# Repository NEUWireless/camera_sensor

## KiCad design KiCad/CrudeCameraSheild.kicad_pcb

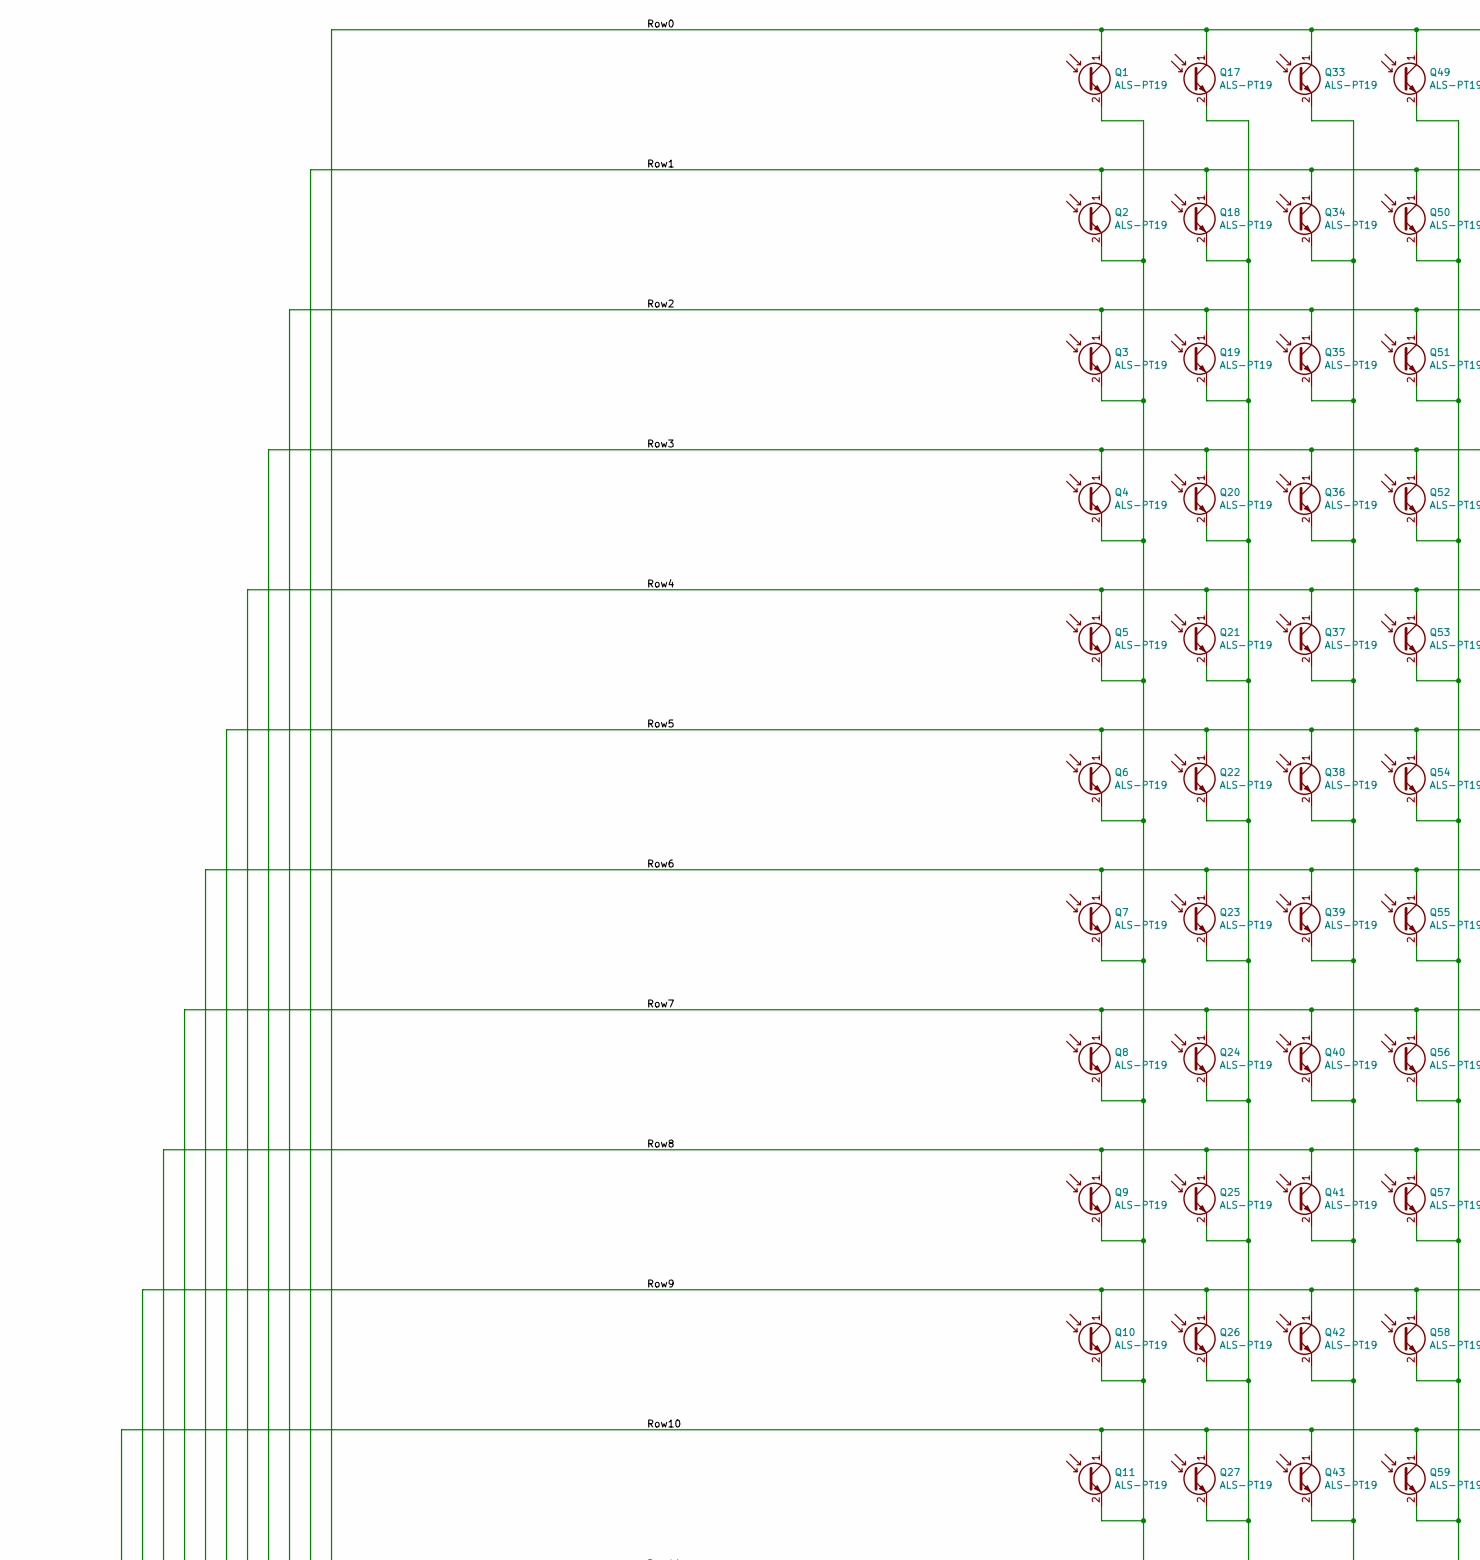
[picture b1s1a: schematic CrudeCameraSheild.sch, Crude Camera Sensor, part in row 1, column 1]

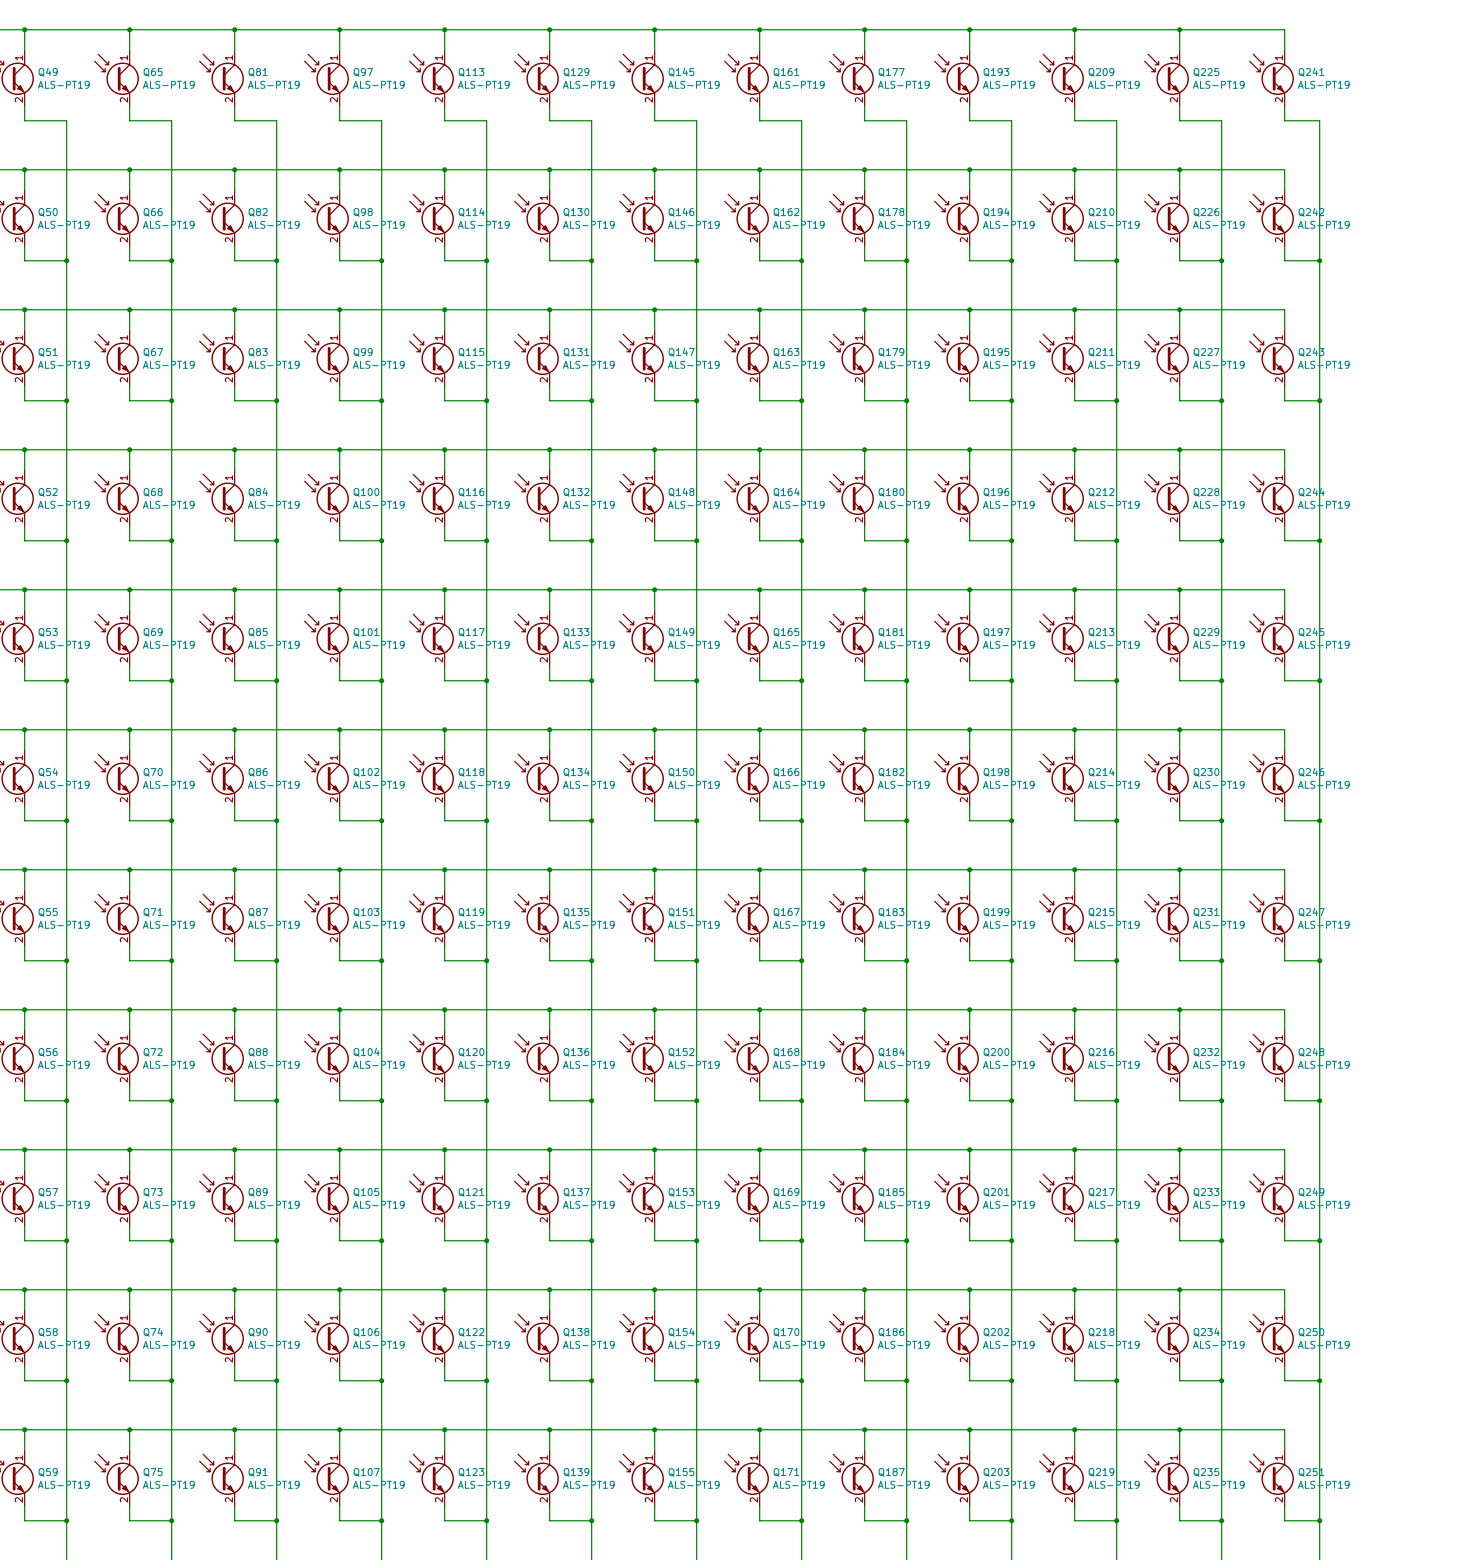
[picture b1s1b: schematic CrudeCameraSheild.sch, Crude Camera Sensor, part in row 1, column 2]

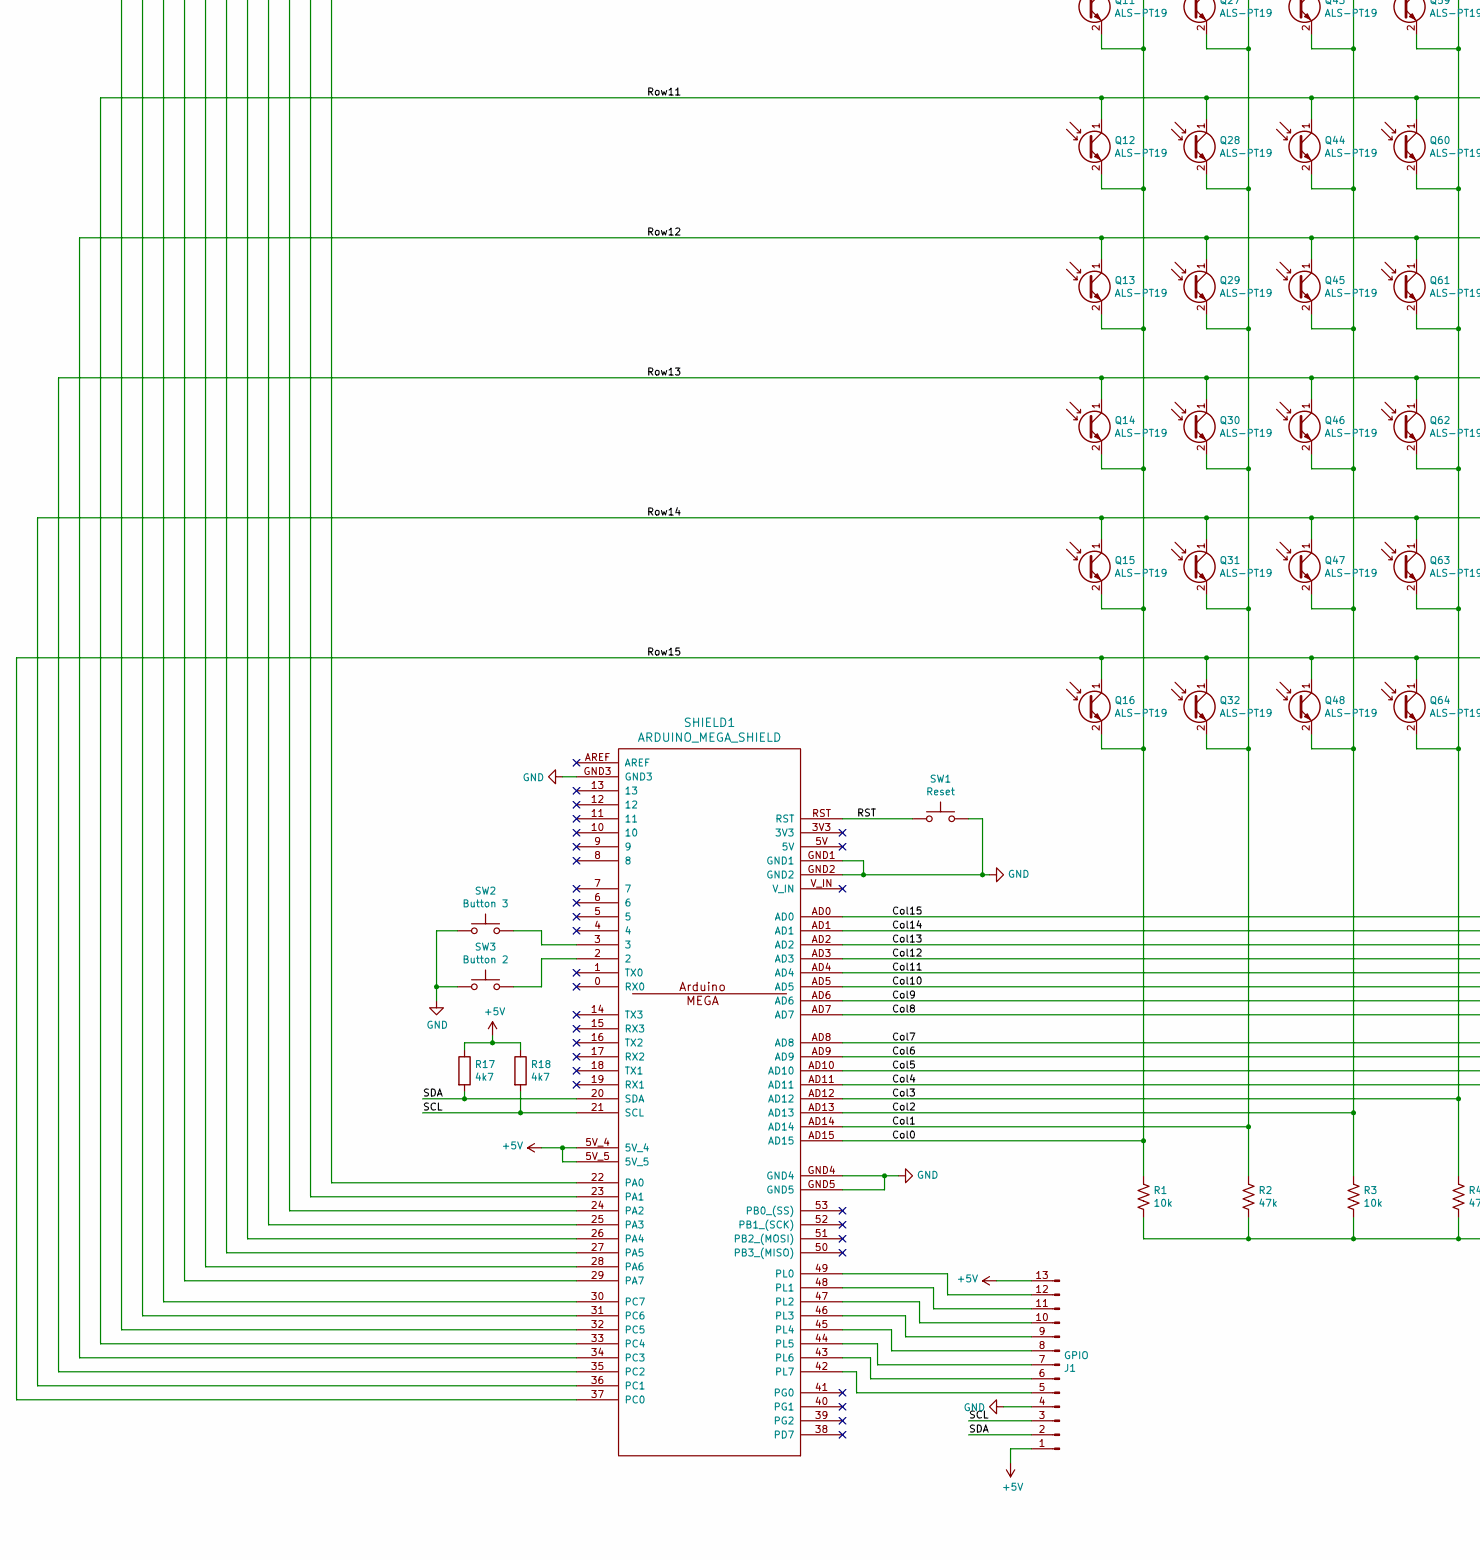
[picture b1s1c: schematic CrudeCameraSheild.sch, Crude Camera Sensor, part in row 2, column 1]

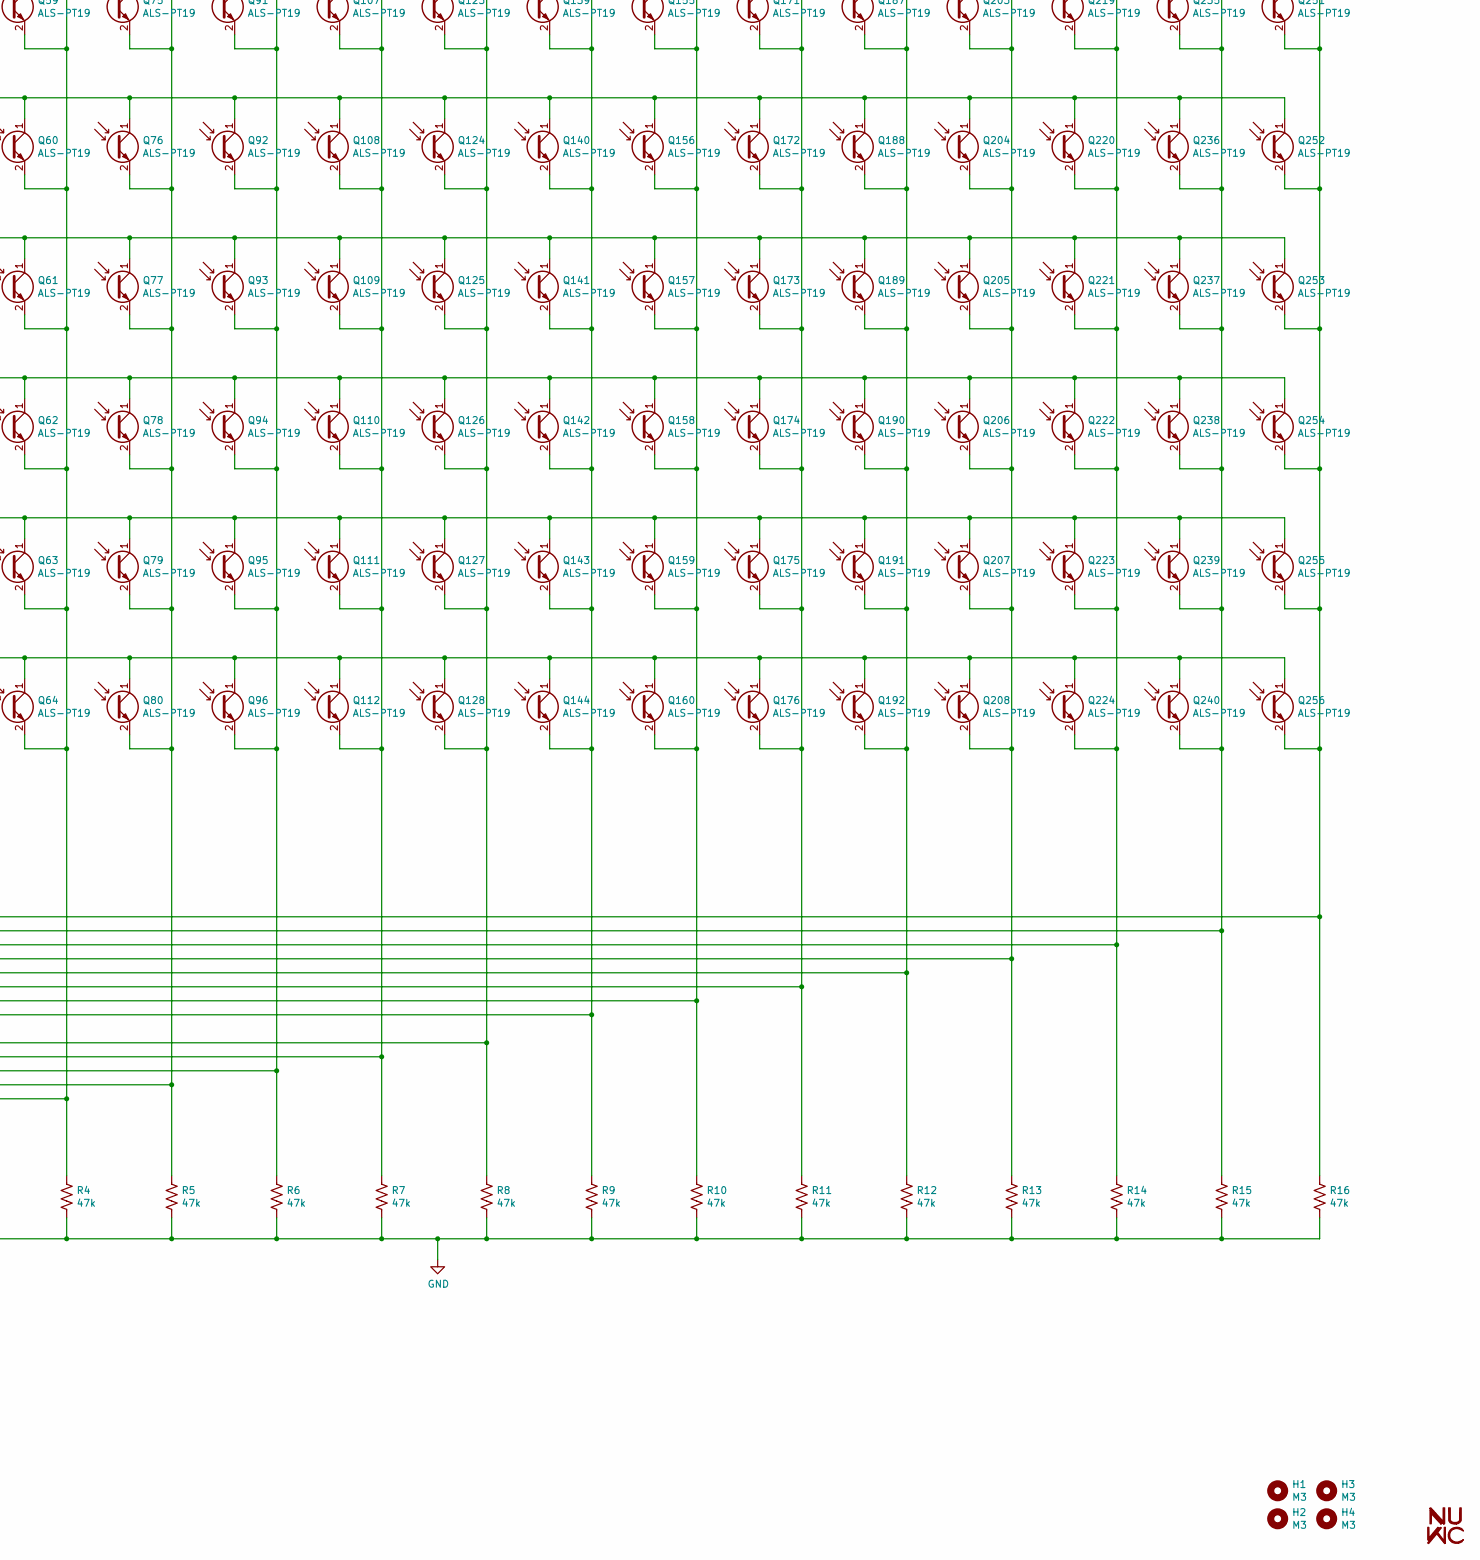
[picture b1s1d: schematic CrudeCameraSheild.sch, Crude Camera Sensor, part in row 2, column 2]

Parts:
G1: LOGO; WirelessClub
H1, H2, H3, H4: M3; MountingHole_3.2mm_M3
J1: GPIO; PinHeader_1x13_P2.54mm_Horizontal
Q1, Q2, Q3, Q4, Q5, Q6, Q7, Q8, Q9, Q10, Q11, Q12, Q13, Q14, Q15, Q16, Q17, Q18, Q19, Q20, Q21, Q22, Q23, Q24, Q25, Q26, Q27, Q28, Q29, Q30, Q31, Q32, Q33, Q34, Q35, Q36, Q37, Q38, Q39, Q40, Q41, Q42, Q43, Q44, Q45, Q46, Q47, Q48, Q49, Q50, Q51, Q52, Q53, Q54, Q55, Q56, Q57, Q58, Q59, Q60, Q61, Q62, Q63, Q64, Q65, Q66, Q67, Q68, Q69, Q70, Q71, Q72, Q73, Q74, Q75, Q76, Q77, Q78, Q79, Q80, Q81, Q82, Q83, Q84, Q85, Q86, Q87, Q88, Q89, Q90, Q91, Q92, Q93, Q94, Q95, Q96, Q97, Q98, Q99, Q100, Q101, Q102, Q103, Q104, Q105, Q106, Q107, Q108, Q109, Q110, Q111, Q112, Q113, Q114, Q115, Q116, Q117, Q118, Q119, Q120, Q121, Q122, Q123, Q124, Q125, Q126, Q127, Q128, Q129, Q130, Q131, Q132, Q133, Q134, Q135, Q136, Q137, Q138, Q139, Q140, Q141, Q142, Q143, Q144, Q145, Q146, Q147, Q148, Q149, Q150, Q151, Q152, Q153, Q154, Q155, Q156, Q157, Q158, Q159, Q160, Q161, Q162, Q163, Q164, Q165, Q166, Q167, Q168, Q169, Q170, Q171, Q172, Q173, Q174, Q175, Q176, Q177, Q178, Q179, Q180, Q181, Q182, Q183, Q184, Q185, Q186, Q187, Q188, Q189, Q190, Q191, Q192, Q193, Q194, Q195, Q196, Q197, Q198, Q199, Q200, Q201, Q202, Q203, Q204, Q205, Q206, Q207, Q208, Q209, Q210, Q211, Q212, Q213, Q214, Q215, Q216, Q217, Q218, Q219, Q220, Q221, Q222, Q223, Q224, Q225, Q226, Q227, Q228, Q229, Q230, Q231, Q232, Q233, Q234, Q235, Q236, Q237, Q238, Q239, Q240, Q241, Q242, Q243, Q244, Q245, Q246, Q247, Q248, Q249, Q250, Q251, Q252, Q253, Q254, Q255, Q256: ALS-PT19; LED_0603_1608Metric_Pad1.05x0.95mm_HandSolder
R1, R3: 10k; R_1206_3216Metric_Pad1.42x1.75mm_HandSolder
R2, R4, R5, R6, R7, R8, R9, R10, R11, R12, R13, R14, R15, R16: 47k; R_1206_3216Metric_Pad1.42x1.75mm_HandSolder
R17, R18: 4k7; R_1206_3216Metric_Pad1.42x1.75mm_HandSolder
SHIELD1: ARDUINO_MEGA_SHIELD; ARDUINO MEGA SHIELD
SW1: Reset; SW_Push_1P1T_NO_6x6mm_H9.5mm
SW2: Button 3; SW_Push_1P1T_NO_6x6mm_H9.5mm
SW3: Button 2; SW_Push_1P1T_NO_6x6mm_H9.5mm

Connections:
+5V: J1.1, J1.13, R17.1, R18.1, SHIELD1.5V_4, SHIELD1.5V_5
/Col0: Q1.2 (E), Q2.2 (E), Q3.2 (E), Q4.2 (E), Q5.2 (E), Q6.2 (E), Q7.2 (E), Q8.2 (E), Q9.2 (E), Q10.2 (E), Q11.2 (E), Q12.2 (E), Q13.2 (E), Q14.2 (E), Q15.2 (E), Q16.2 (E), R1.1, SHIELD1.AD15
/Col1: Q17.2 (E), Q18.2 (E), Q19.2 (E), Q20.2 (E), Q21.2 (E), Q22.2 (E), Q23.2 (E), Q24.2 (E), Q25.2 (E), Q26.2 (E), Q27.2 (E), Q28.2 (E), Q29.2 (E), Q30.2 (E), Q31.2 (E), Q32.2 (E), R2.1, SHIELD1.AD14
/Col2: Q33.2 (E), Q34.2 (E), Q35.2 (E), Q36.2 (E), Q37.2 (E), Q38.2 (E), Q39.2 (E), Q40.2 (E), Q41.2 (E), Q42.2 (E), Q43.2 (E), Q44.2 (E), Q45.2 (E), Q46.2 (E), Q47.2 (E), Q48.2 (E), R3.1, SHIELD1.AD13
/Col3: Q49.2 (E), Q50.2 (E), Q51.2 (E), Q52.2 (E), Q53.2 (E), Q54.2 (E), Q55.2 (E), Q56.2 (E), Q57.2 (E), Q58.2 (E), Q59.2 (E), Q60.2 (E), Q61.2 (E), Q62.2 (E), Q63.2 (E), Q64.2 (E), R4.1, SHIELD1.AD12
/Col4: Q65.2 (E), Q66.2 (E), Q67.2 (E), Q68.2 (E), Q69.2 (E), Q70.2 (E), Q71.2 (E), Q72.2 (E), Q73.2 (E), Q74.2 (E), Q75.2 (E), Q76.2 (E), Q77.2 (E), Q78.2 (E), Q79.2 (E), Q80.2 (E), R5.1, SHIELD1.AD11
/Col5: Q81.2 (E), Q82.2 (E), Q83.2 (E), Q84.2 (E), Q85.2 (E), Q86.2 (E), Q87.2 (E), Q88.2 (E), Q89.2 (E), Q90.2 (E), Q91.2 (E), Q92.2 (E), Q93.2 (E), Q94.2 (E), Q95.2 (E), Q96.2 (E), R6.1, SHIELD1.AD10
/Col6: Q97.2 (E), Q98.2 (E), Q99.2 (E), Q100.2 (E), Q101.2 (E), Q102.2 (E), Q103.2 (E), Q104.2 (E), Q105.2 (E), Q106.2 (E), Q107.2 (E), Q108.2 (E), Q109.2 (E), Q110.2 (E), Q111.2 (E), Q112.2 (E), R7.1, SHIELD1.AD9
/Col7: Q113.2 (E), Q114.2 (E), Q115.2 (E), Q116.2 (E), Q117.2 (E), Q118.2 (E), Q119.2 (E), Q120.2 (E), Q121.2 (E), Q122.2 (E), Q123.2 (E), Q124.2 (E), Q125.2 (E), Q126.2 (E), Q127.2 (E), Q128.2 (E), R8.1, SHIELD1.AD8
/Col8: Q129.2 (E), Q130.2 (E), Q131.2 (E), Q132.2 (E), Q133.2 (E), Q134.2 (E), Q135.2 (E), Q136.2 (E), Q137.2 (E), Q138.2 (E), Q139.2 (E), Q140.2 (E), Q141.2 (E), Q142.2 (E), Q143.2 (E), Q144.2 (E), R9.1, SHIELD1.AD7
/Col9: Q145.2 (E), Q146.2 (E), Q147.2 (E), Q148.2 (E), Q149.2 (E), Q150.2 (E), Q151.2 (E), Q152.2 (E), Q153.2 (E), Q154.2 (E), Q155.2 (E), Q156.2 (E), Q157.2 (E), Q158.2 (E), Q159.2 (E), Q160.2 (E), R10.1, SHIELD1.AD6
/Col10: Q161.2 (E), Q162.2 (E), Q163.2 (E), Q164.2 (E), Q165.2 (E), Q166.2 (E), Q167.2 (E), Q168.2 (E), Q169.2 (E), Q170.2 (E), Q171.2 (E), Q172.2 (E), Q173.2 (E), Q174.2 (E), Q175.2 (E), Q176.2 (E), R11.1, SHIELD1.AD5
/Col11: Q177.2 (E), Q178.2 (E), Q179.2 (E), Q180.2 (E), Q181.2 (E), Q182.2 (E), Q183.2 (E), Q184.2 (E), Q185.2 (E), Q186.2 (E), Q187.2 (E), Q188.2 (E), Q189.2 (E), Q190.2 (E), Q191.2 (E), Q192.2 (E), R12.1, SHIELD1.AD4
/Col12: Q193.2 (E), Q194.2 (E), Q195.2 (E), Q196.2 (E), Q197.2 (E), Q198.2 (E), Q199.2 (E), Q200.2 (E), Q201.2 (E), Q202.2 (E), Q203.2 (E), Q204.2 (E), Q205.2 (E), Q206.2 (E), Q207.2 (E), Q208.2 (E), R13.1, SHIELD1.AD3
/Col13: Q209.2 (E), Q210.2 (E), Q211.2 (E), Q212.2 (E), Q213.2 (E), Q214.2 (E), Q215.2 (E), Q216.2 (E), Q217.2 (E), Q218.2 (E), Q219.2 (E), Q220.2 (E), Q221.2 (E), Q222.2 (E), Q223.2 (E), Q224.2 (E), R14.1, SHIELD1.AD2
/Col14: Q225.2 (E), Q226.2 (E), Q227.2 (E), Q228.2 (E), Q229.2 (E), Q230.2 (E), Q231.2 (E), Q232.2 (E), Q233.2 (E), Q234.2 (E), Q235.2 (E), Q236.2 (E), Q237.2 (E), Q238.2 (E), Q239.2 (E), Q240.2 (E), R15.1, SHIELD1.AD1
/Col15: Q241.2 (E), Q242.2 (E), Q243.2 (E), Q244.2 (E), Q245.2 (E), Q246.2 (E), Q247.2 (E), Q248.2 (E), Q249.2 (E), Q250.2 (E), Q251.2 (E), Q252.2 (E), Q253.2 (E), Q254.2 (E), Q255.2 (E), Q256.2 (E), R16.1, SHIELD1.AD0
/RST: SHIELD1.RST, SW1.1
/Row0: Q1.1 (C), Q17.1 (C), Q33.1 (C), Q49.1 (C), Q65.1 (C), Q81.1 (C), Q97.1 (C), Q113.1 (C), Q129.1 (C), Q145.1 (C), Q161.1 (C), Q177.1 (C), Q193.1 (C), Q209.1 (C), Q225.1 (C), Q241.1 (C), SHIELD1.22 (PA0)
/Row1: Q2.1 (C), Q18.1 (C), Q34.1 (C), Q50.1 (C), Q66.1 (C), Q82.1 (C), Q98.1 (C), Q114.1 (C), Q130.1 (C), Q146.1 (C), Q162.1 (C), Q178.1 (C), Q194.1 (C), Q210.1 (C), Q226.1 (C), Q242.1 (C), SHIELD1.23 (PA1)
/Row2: Q3.1 (C), Q19.1 (C), Q35.1 (C), Q51.1 (C), Q67.1 (C), Q83.1 (C), Q99.1 (C), Q115.1 (C), Q131.1 (C), Q147.1 (C), Q163.1 (C), Q179.1 (C), Q195.1 (C), Q211.1 (C), Q227.1 (C), Q243.1 (C), SHIELD1.24 (PA2)
/Row3: Q4.1 (C), Q20.1 (C), Q36.1 (C), Q52.1 (C), Q68.1 (C), Q84.1 (C), Q100.1 (C), Q116.1 (C), Q132.1 (C), Q148.1 (C), Q164.1 (C), Q180.1 (C), Q196.1 (C), Q212.1 (C), Q228.1 (C), Q244.1 (C), SHIELD1.25 (PA3)
/Row4: Q5.1 (C), Q21.1 (C), Q37.1 (C), Q53.1 (C), Q69.1 (C), Q85.1 (C), Q101.1 (C), Q117.1 (C), Q133.1 (C), Q149.1 (C), Q165.1 (C), Q181.1 (C), Q197.1 (C), Q213.1 (C), Q229.1 (C), Q245.1 (C), SHIELD1.26 (PA4)
/Row5: Q6.1 (C), Q22.1 (C), Q38.1 (C), Q54.1 (C), Q70.1 (C), Q86.1 (C), Q102.1 (C), Q118.1 (C), Q134.1 (C), Q150.1 (C), Q166.1 (C), Q182.1 (C), Q198.1 (C), Q214.1 (C), Q230.1 (C), Q246.1 (C), SHIELD1.27 (PA5)
/Row6: Q7.1 (C), Q23.1 (C), Q39.1 (C), Q55.1 (C), Q71.1 (C), Q87.1 (C), Q103.1 (C), Q119.1 (C), Q135.1 (C), Q151.1 (C), Q167.1 (C), Q183.1 (C), Q199.1 (C), Q215.1 (C), Q231.1 (C), Q247.1 (C), SHIELD1.28 (PA6)
/Row7: Q8.1 (C), Q24.1 (C), Q40.1 (C), Q56.1 (C), Q72.1 (C), Q88.1 (C), Q104.1 (C), Q120.1 (C), Q136.1 (C), Q152.1 (C), Q168.1 (C), Q184.1 (C), Q200.1 (C), Q216.1 (C), Q232.1 (C), Q248.1 (C), SHIELD1.29 (PA7)
/Row8: Q9.1 (C), Q25.1 (C), Q41.1 (C), Q57.1 (C), Q73.1 (C), Q89.1 (C), Q105.1 (C), Q121.1 (C), Q137.1 (C), Q153.1 (C), Q169.1 (C), Q185.1 (C), Q201.1 (C), Q217.1 (C), Q233.1 (C), Q249.1 (C), SHIELD1.30 (PC7)
/Row9: Q10.1 (C), Q26.1 (C), Q42.1 (C), Q58.1 (C), Q74.1 (C), Q90.1 (C), Q106.1 (C), Q122.1 (C), Q138.1 (C), Q154.1 (C), Q170.1 (C), Q186.1 (C), Q202.1 (C), Q218.1 (C), Q234.1 (C), Q250.1 (C), SHIELD1.31 (PC6)
/Row10: Q11.1 (C), Q27.1 (C), Q43.1 (C), Q59.1 (C), Q75.1 (C), Q91.1 (C), Q107.1 (C), Q123.1 (C), Q139.1 (C), Q155.1 (C), Q171.1 (C), Q187.1 (C), Q203.1 (C), Q219.1 (C), Q235.1 (C), Q251.1 (C), SHIELD1.32 (PC5)
/Row11: Q12.1 (C), Q28.1 (C), Q44.1 (C), Q60.1 (C), Q76.1 (C), Q92.1 (C), Q108.1 (C), Q124.1 (C), Q140.1 (C), Q156.1 (C), Q172.1 (C), Q188.1 (C), Q204.1 (C), Q220.1 (C), Q236.1 (C), Q252.1 (C), SHIELD1.33 (PC4)
/Row12: Q13.1 (C), Q29.1 (C), Q45.1 (C), Q61.1 (C), Q77.1 (C), Q93.1 (C), Q109.1 (C), Q125.1 (C), Q141.1 (C), Q157.1 (C), Q173.1 (C), Q189.1 (C), Q205.1 (C), Q221.1 (C), Q237.1 (C), Q253.1 (C), SHIELD1.34 (PC3)
/Row13: Q14.1 (C), Q30.1 (C), Q46.1 (C), Q62.1 (C), Q78.1 (C), Q94.1 (C), Q110.1 (C), Q126.1 (C), Q142.1 (C), Q158.1 (C), Q174.1 (C), Q190.1 (C), Q206.1 (C), Q222.1 (C), Q238.1 (C), Q254.1 (C), SHIELD1.35 (PC2)
/Row14: Q15.1 (C), Q31.1 (C), Q47.1 (C), Q63.1 (C), Q79.1 (C), Q95.1 (C), Q111.1 (C), Q127.1 (C), Q143.1 (C), Q159.1 (C), Q175.1 (C), Q191.1 (C), Q207.1 (C), Q223.1 (C), Q239.1 (C), Q255.1 (C), SHIELD1.36 (PC1)
/Row15: Q16.1 (C), Q32.1 (C), Q48.1 (C), Q64.1 (C), Q80.1 (C), Q96.1 (C), Q112.1 (C), Q128.1 (C), Q144.1 (C), Q160.1 (C), Q176.1 (C), Q192.1 (C), Q208.1 (C), Q224.1 (C), Q240.1 (C), Q256.1 (C), SHIELD1.37 (PC0)
/SCL: J1.3, R18.2, SHIELD1.21 (SCL)
/SDA: J1.2, R17.2, SHIELD1.20 (SDA)
GND: J1.4, R1.2, R2.2, R3.2, R4.2, R5.2, R6.2, R7.2, R8.2, R9.2, R10.2, R11.2, R12.2, R13.2, R14.2, R15.2, R16.2, SHIELD1.GND1, SHIELD1.GND2, SHIELD1.GND3, SHIELD1.GND4, SHIELD1.GND5, SW1.2, SW2.1, SW3.1
unnamed: J1.5, SHIELD1.42 (PL7)
unnamed: J1.6, SHIELD1.43 (PL6)
unnamed: J1.7, SHIELD1.44 (PL5)
unnamed: J1.8, SHIELD1.45 (PL4)
unnamed: J1.9, SHIELD1.46 (PL3)
unnamed: J1.10, SHIELD1.47 (PL2)
unnamed: J1.11, SHIELD1.48 (PL1)
unnamed: J1.12, SHIELD1.49 (PL0)
unnamed: SHIELD1.2, SW3.2
unnamed: SHIELD1.3, SW2.2

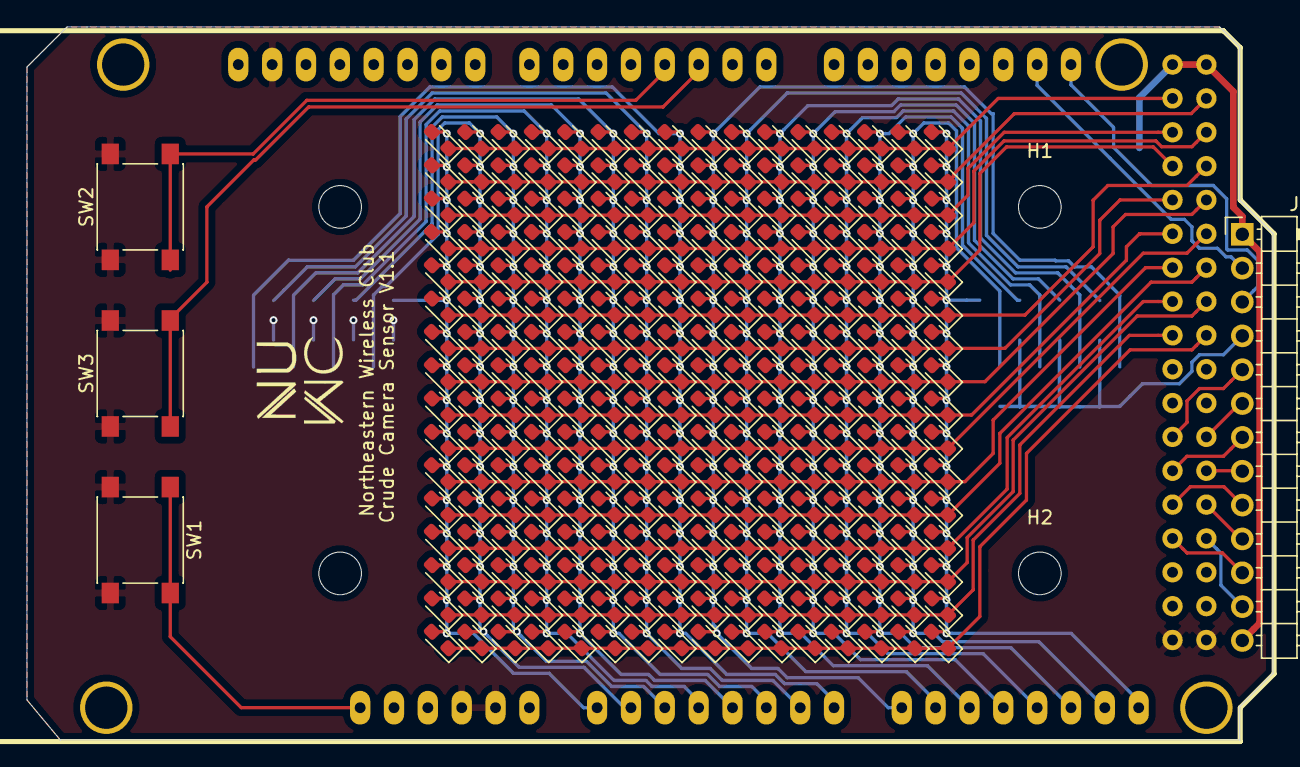
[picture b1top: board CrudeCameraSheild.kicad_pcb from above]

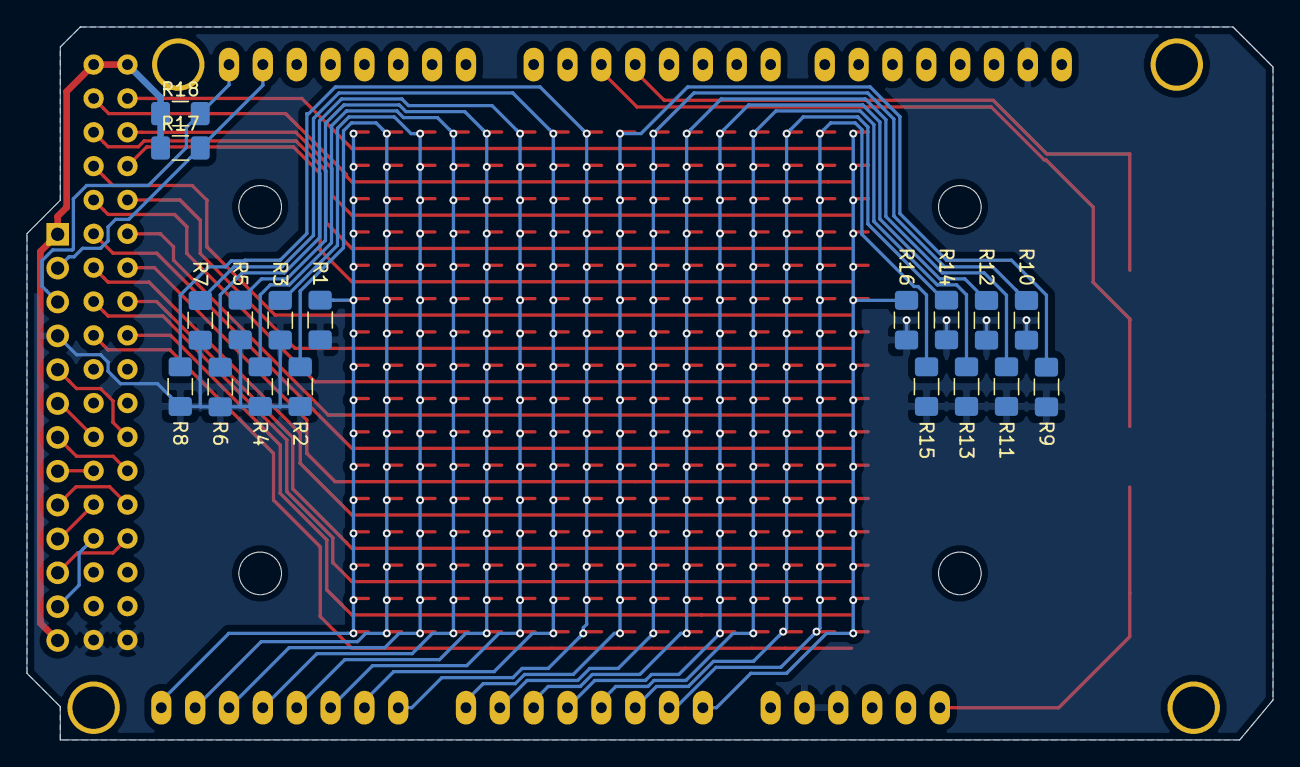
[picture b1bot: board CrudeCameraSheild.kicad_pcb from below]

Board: 2 copper layers, 93.5 x 53.5 mm, 284 parts (18 on the bottom side), 47 nets.

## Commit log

2020-02-05 Added hardware design files.
2020-02-05 Corrected spelling of sensor on silkscreen. Updated resistor values.
